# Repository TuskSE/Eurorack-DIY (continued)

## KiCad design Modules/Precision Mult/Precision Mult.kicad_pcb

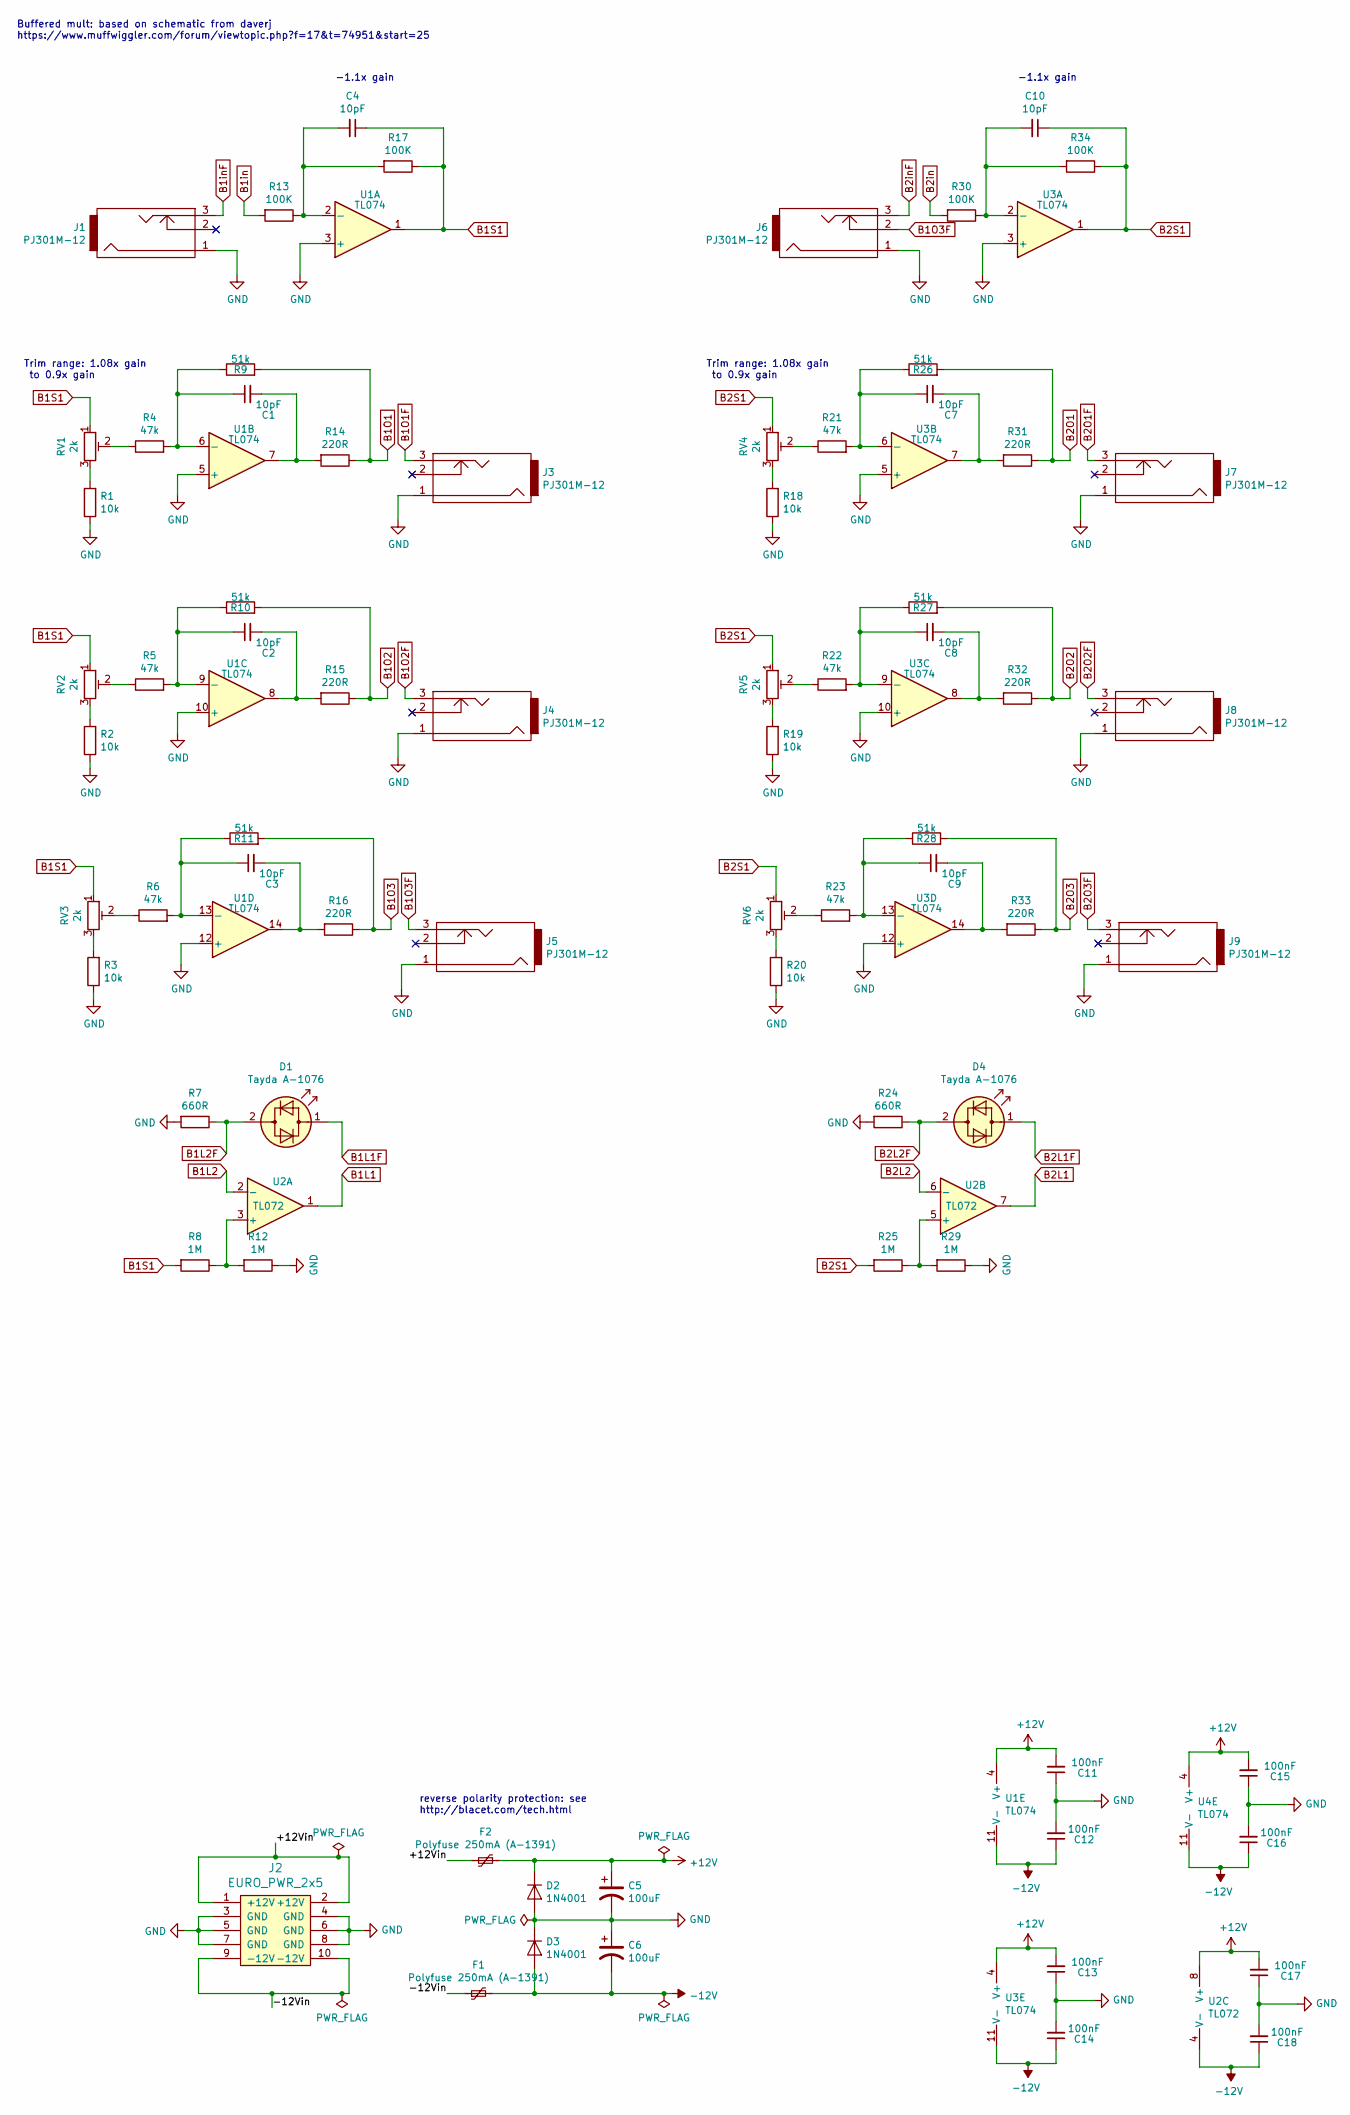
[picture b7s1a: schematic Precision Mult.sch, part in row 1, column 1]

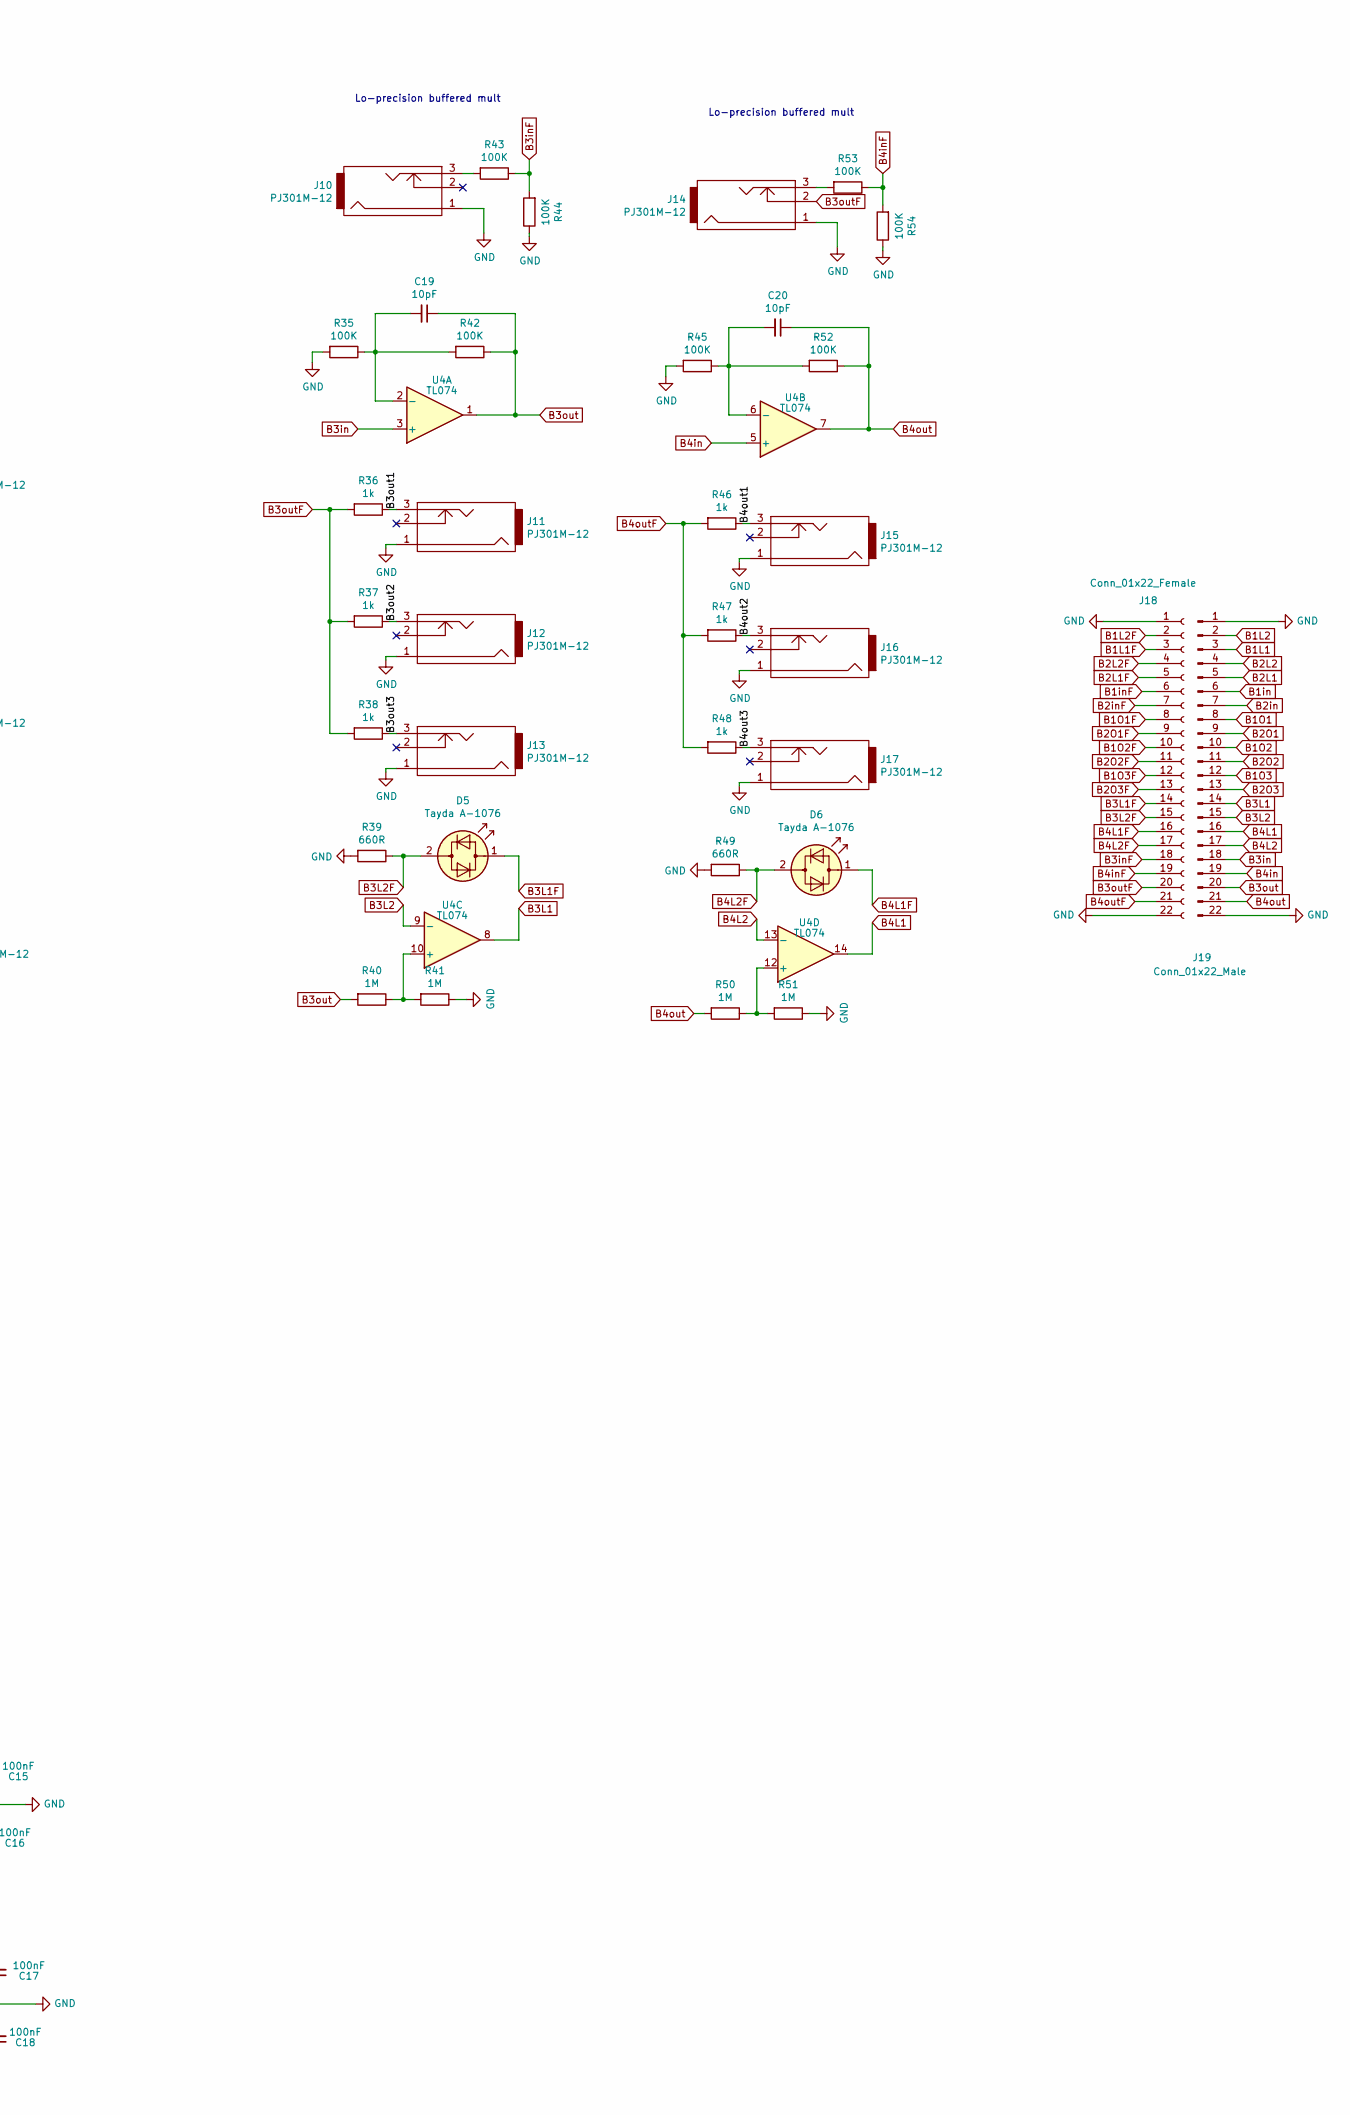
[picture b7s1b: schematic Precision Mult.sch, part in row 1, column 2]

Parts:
C1, C2, C3, C4, C7, C8, C9, C10, C19, C20: 10pF; C_0805_2012Metric_Pad1.15x1.40mm_HandSolder_smallText
C5, C6: 100uF; CP_Radial_D6.3mm_P2.50mm
C11, C12, C13, C14, C15, C16, C17, C18: 100nF; C_0805_2012Metric_Pad1.15x1.40mm_HandSolder_smallText
D1, D4, D5, D6: Tayda A-1076; LED_D3.0mm
D2, D3: 1N4001; D_DO-41_SOD81_P10.16mm_Horizontal
F1, F2: Polyfuse 250mA (A-1391); C_Disc_D7.5mm_W2.5mm_P5.00mm
J1, J3, J4, J5, J6, J7, J8, J9, J10, J11, J12, J13, J14, J15, J16, J17: PJ301M-12; PJ301M-12_Compact
J2: EURO_PWR_2x5; Eurorack_power_header
J18: Conn_01x22_Female; PinSocket_1x22_P2.54mm_Vertical
J19: Conn_01x22_Male; PinSocket_1x22_P2.54mm_Vertical
R1, R2, R3, R18, R19, R20: 10k; R_0805_2012Metric_Pad1.15x1.40mm_HandSolder
R4, R5, R6, R21, R22, R23: 47k; R_0805_2012Metric_Pad1.15x1.40mm_HandSolder
R7, R24, R39, R49: 660R; R_0805_2012Metric_Pad1.15x1.40mm_HandSolder
R8, R12, R25, R29, R40, R41, R50, R51: 1M; R_0805_2012Metric_Pad1.15x1.40mm_HandSolder
R9, R10, R11, R26, R27, R28: 51k; R_0805_2012Metric_Pad1.15x1.40mm_HandSolder
R13, R17, R30, R34, R35, R42, R43, R44, R45, R52, R53, R54: 100K; R_0805_2012Metric_Pad1.15x1.40mm_HandSolder
R14, R15, R16, R31, R32, R33: 220R; R_0805_2012Metric_Pad1.15x1.40mm_HandSolder
R36, R37, R38, R46, R47, R48: 1k; R_0805_2012Metric_Pad1.15x1.40mm_HandSolder
RV1, RV2, RV3, RV4, RV5, RV6: 2k; Potentiometer_Bourns_3296W_Vertical
U1, U3, U4: TL074; SOIC-14_3.9x8.7mm_P1.27mm
U2: TL072; SOIC-8_3.9x4.9mm_P1.27mm

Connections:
+12V: C5.1, C11.2, C13.2, C15.2, C17.2, D2.1 (K), F2.1, U1.4 (V+), U2.8 (V+), U3.4 (V+), U4.4 (V+)
-12V: C6.2, C12.1, C14.1, C16.1, C18.1, D3.2 (A), F1.2, U1.11 (V-), U2.4 (V-), U3.11 (V-), U4.11 (V-)
/+12Vin: F2.2, J2.1 (+12V), J2.2 (+12V)
/-12Vin: F1.1, J2.9 (-12V), J2.10 (-12V)
/B3out1: J11.3, R36.1
/B3out2: J12.3, R37.1
/B3out3: J13.3, R38.1
/B4out1: J15.3, R46.1
/B4out2: J16.3, R47.1
/B4out3: J17.3, R48.1
B1L1: J19.3, U2.1
B1L1F: D1.1 (KA), J18.3
B1L2: J19.2, U2.2 (-)
B1L2F: D1.2 (AK), J18.2, R7.1
B1O1: J19.8, R9.2, R14.1
B1O1F: J3.3, J18.8
B1O2: J19.10, R10.2, R15.1
B1O2F: J4.3, J18.10
B1O3: J19.12, R11.2, R16.1
B1O3F: J5.3, J6.2, J18.12
B1S1: C4.1, R8.2, R17.1, RV1.1, RV2.1, RV3.1, U1.1
B1in: J19.6, R13.2
B1inF: J1.3, J18.6
B2L1: J19.5, U2.7
B2L1F: D4.1 (KA), J18.5
B2L2: J19.4, U2.6 (-)
B2L2F: D4.2 (AK), J18.4, R24.1
B2O1: J19.9, R26.2, R31.1
B2O1F: J7.3, J18.9
B2O2: J19.11, R27.2, R32.1
B2O2F: J8.3, J18.11
B2O3: J19.13, R28.2, R33.1
B2O3F: J9.3, J18.13
B2S1: C10.1, R25.2, R34.1, RV4.1, RV5.1, RV6.1, U3.1
B2in: J19.7, R30.2
B2inF: J6.3, J18.7
B3L1: J19.14, U4.8
B3L1F: D5.1 (KA), J18.14
B3L2: J19.15, U4.9 (-)
B3L2F: D5.2 (AK), J18.15, R39.1
B3in: J19.18, U4.3 (+)
B3inF: J18.18, R43.1, R44.2
B3out: C19.1, J19.20, R40.2, R42.1, U4.1
B3outF: J14.2, J18.20, R36.2, R37.2, R38.2
B4L1: J19.16, U4.14
B4L1F: D6.1 (KA), J18.16
B4L2: J19.17, U4.13 (-)
B4L2F: D6.2 (AK), J18.17, R49.1
B4in: J19.19, U4.5 (+)
B4inF: J18.19, R53.1, R54.2
B4out: C20.1, J19.21, R50.2, R52.1, U4.7
B4outF: J18.21, R46.2, R47.2, R48.2
GND: C5.2, C6.1, C11.1, C12.2, C13.1, C14.2, C15.1, C16.2, C17.1, C18.2, D2.2 (A), D3.1 (K), J1.1, J2.3 (GND), J2.4 (GND), J2.5 (GND), J2.6 (GND), J2.7 (GND), J2.8 (GND), J3.1, J4.1, J5.1, J6.1, J7.1, J8.1, J9.1, J10.1, J11.1, J12.1, J13.1, J14.1, J15.1, J16.1, J17.1, J18.1, J18.22, J19.1, J19.22, R1.1, R2.1, R3.1, R7.2, R12.1, R18.1, R19.1, R20.1, R24.2, R29.1, R35.2, R39.2, R41.1, R44.1, R45.2, R49.2, R51.1, R54.1, U1.3 (+), U1.5 (+), U1.10 (+), U1.12 (+), U3.3 (+), U3.5 (+), U3.10 (+), U3.12 (+)
unnamed: C1.1, R4.2, R9.1, U1.6 (-)
unnamed: C1.2, R14.2, U1.7
unnamed: C2.1, R5.2, R10.1, U1.9 (-)
unnamed: C2.2, R15.2, U1.8
unnamed: C3.1, R6.2, R11.1, U1.13 (-)
unnamed: C3.2, R16.2, U1.14
unnamed: C4.2, R13.1, R17.2, U1.2 (-)
unnamed: C7.1, R21.2, R26.1, U3.6 (-)
unnamed: C7.2, R31.2, U3.7
unnamed: C8.1, R22.2, R27.1, U3.9 (-)
unnamed: C8.2, R32.2, U3.8
unnamed: C9.1, R23.2, R28.1, U3.13 (-)
unnamed: C9.2, R33.2, U3.14
unnamed: C10.2, R30.1, R34.2, U3.2 (-)
unnamed: C19.2, R35.1, R42.2, U4.2 (-)
unnamed: C20.2, R45.1, R52.2, U4.6 (-)
unnamed: J10.3, R43.2
unnamed: J14.3, R53.2
unnamed: R1.2, RV1.3
unnamed: R2.2, RV2.3
unnamed: R3.2, RV3.3
unnamed: R4.1, RV1.2
unnamed: R5.1, RV2.2
unnamed: R6.1, RV3.2
unnamed: R8.1, R12.2, U2.3 (+)
unnamed: R18.2, RV4.3
unnamed: R19.2, RV5.3
unnamed: R20.2, RV6.3
unnamed: R21.1, RV4.2
unnamed: R22.1, RV5.2
unnamed: R23.1, RV6.2
unnamed: R25.1, R29.2, U2.5 (+)
unnamed: R40.1, R41.2, U4.10 (+)
unnamed: R50.1, R51.2, U4.12 (+)

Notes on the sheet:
-1.1x gain
Trim range: 1.08x gain to 0.9x gain
Buffered mult: based on schematic from daverj https://www.muffwiggler.com/forum/viewtopic.php?f=17&t=74951&start=25
reverse polarity protection: see http://blacet.com/tech.html
Lo-precision buffered mult

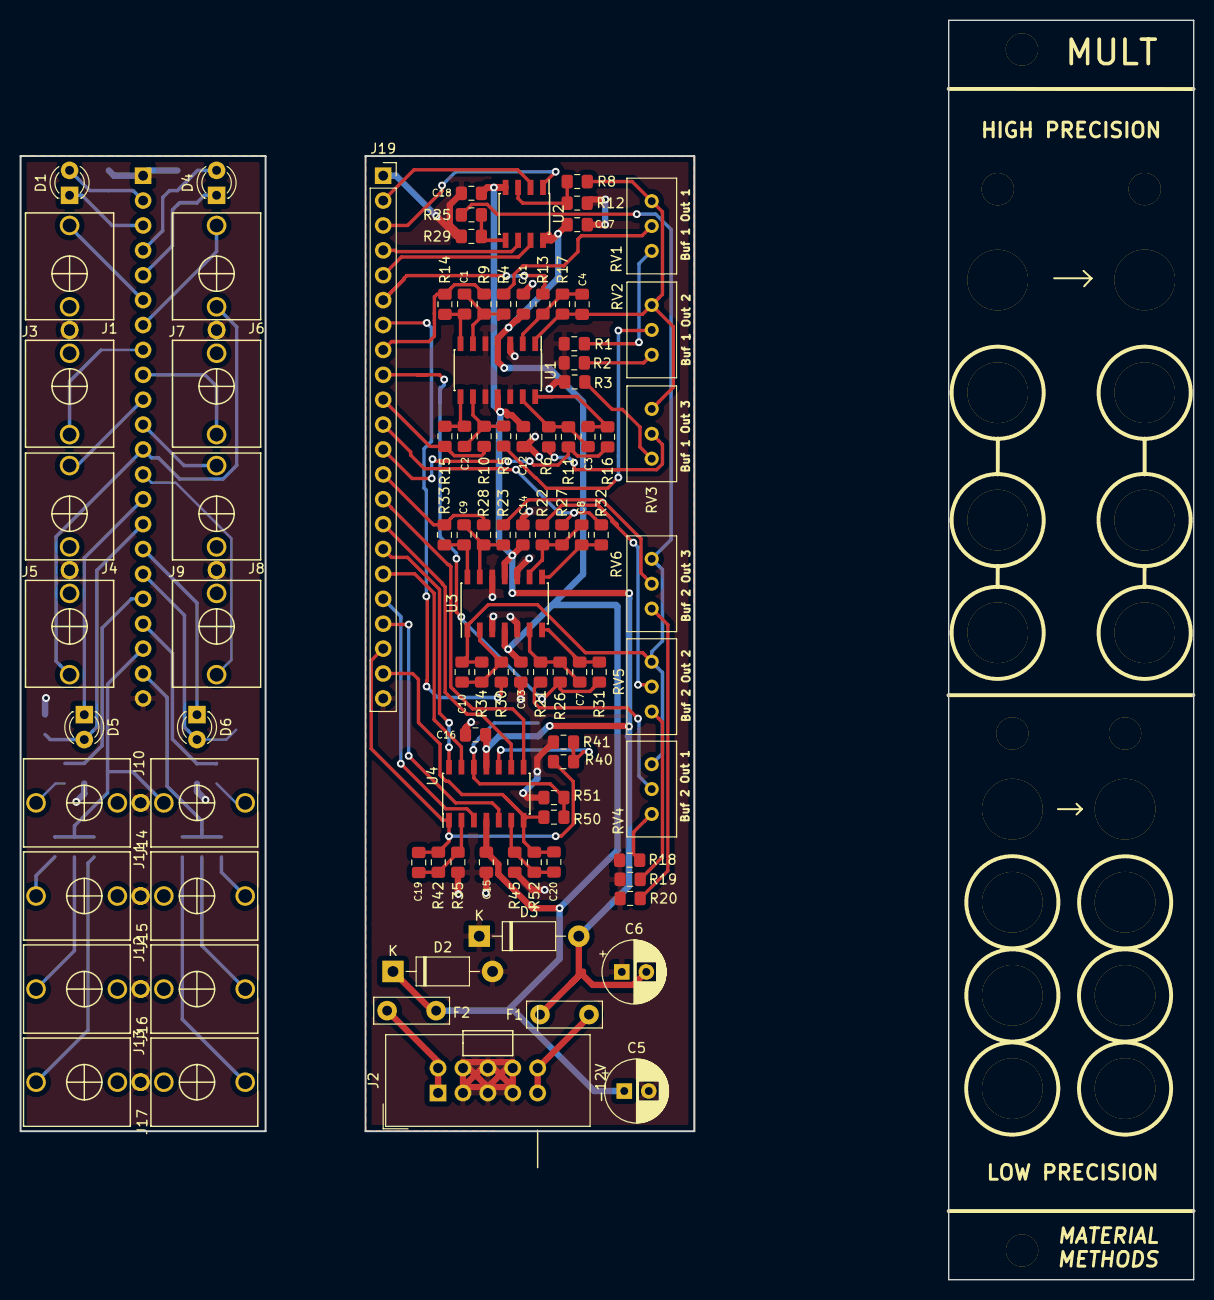
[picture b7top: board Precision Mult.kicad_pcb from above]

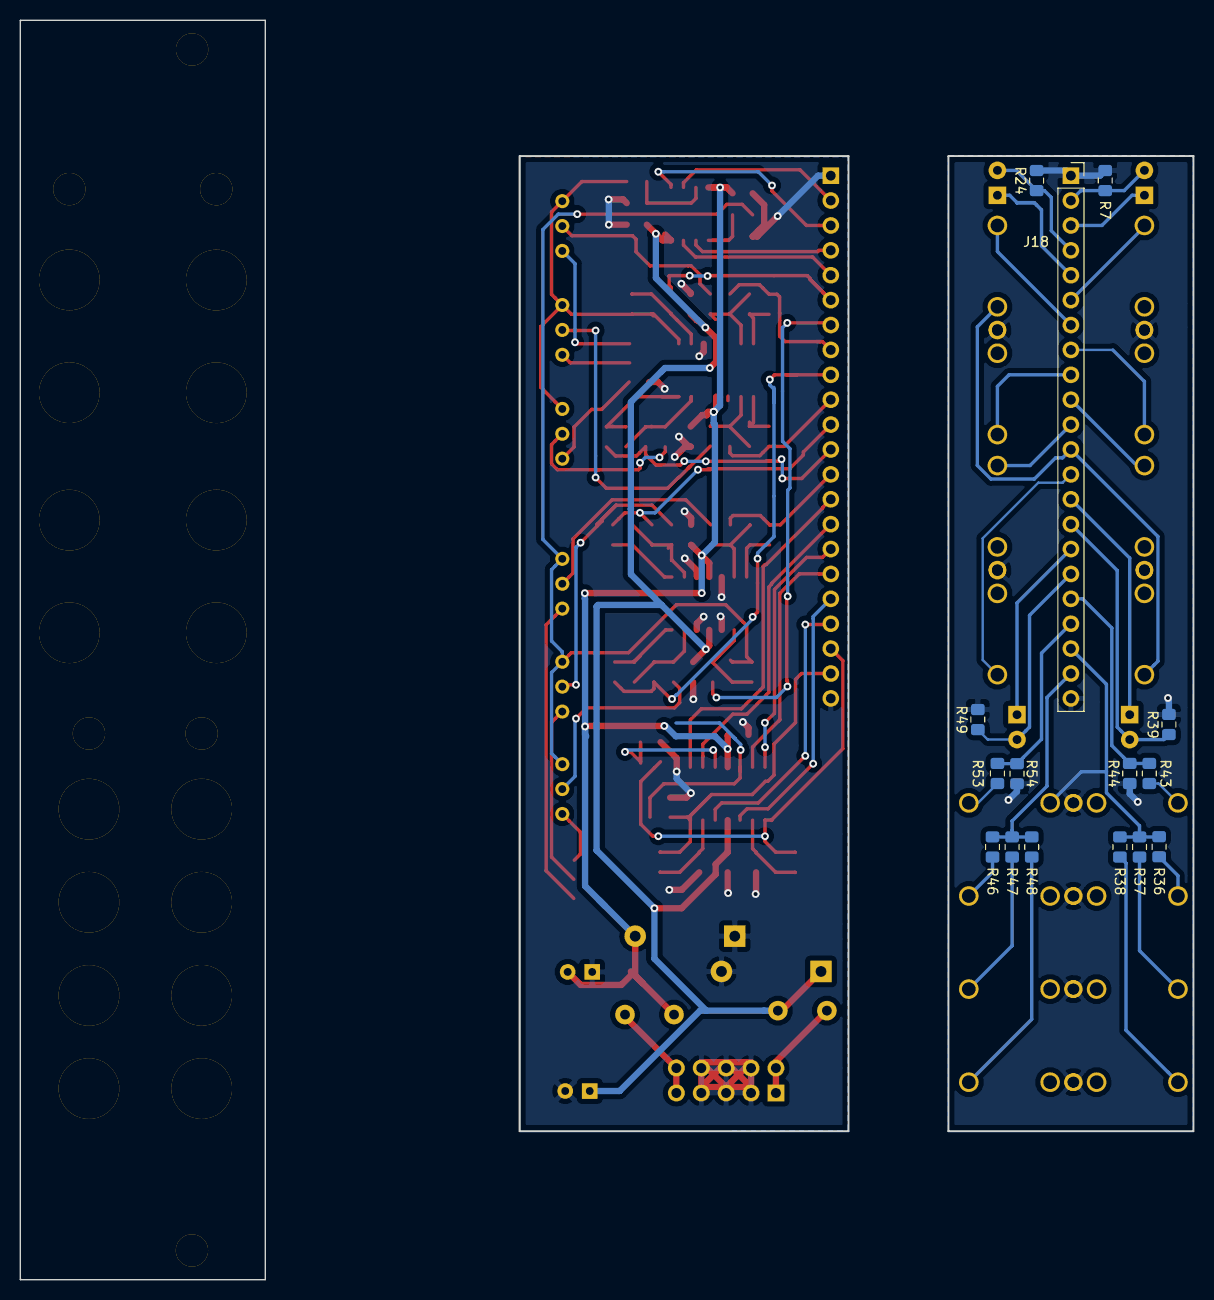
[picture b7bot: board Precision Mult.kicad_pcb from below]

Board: 2 copper layers, 119.7 x 128.5 mm, 111 parts (15 on the bottom side), 87 nets.

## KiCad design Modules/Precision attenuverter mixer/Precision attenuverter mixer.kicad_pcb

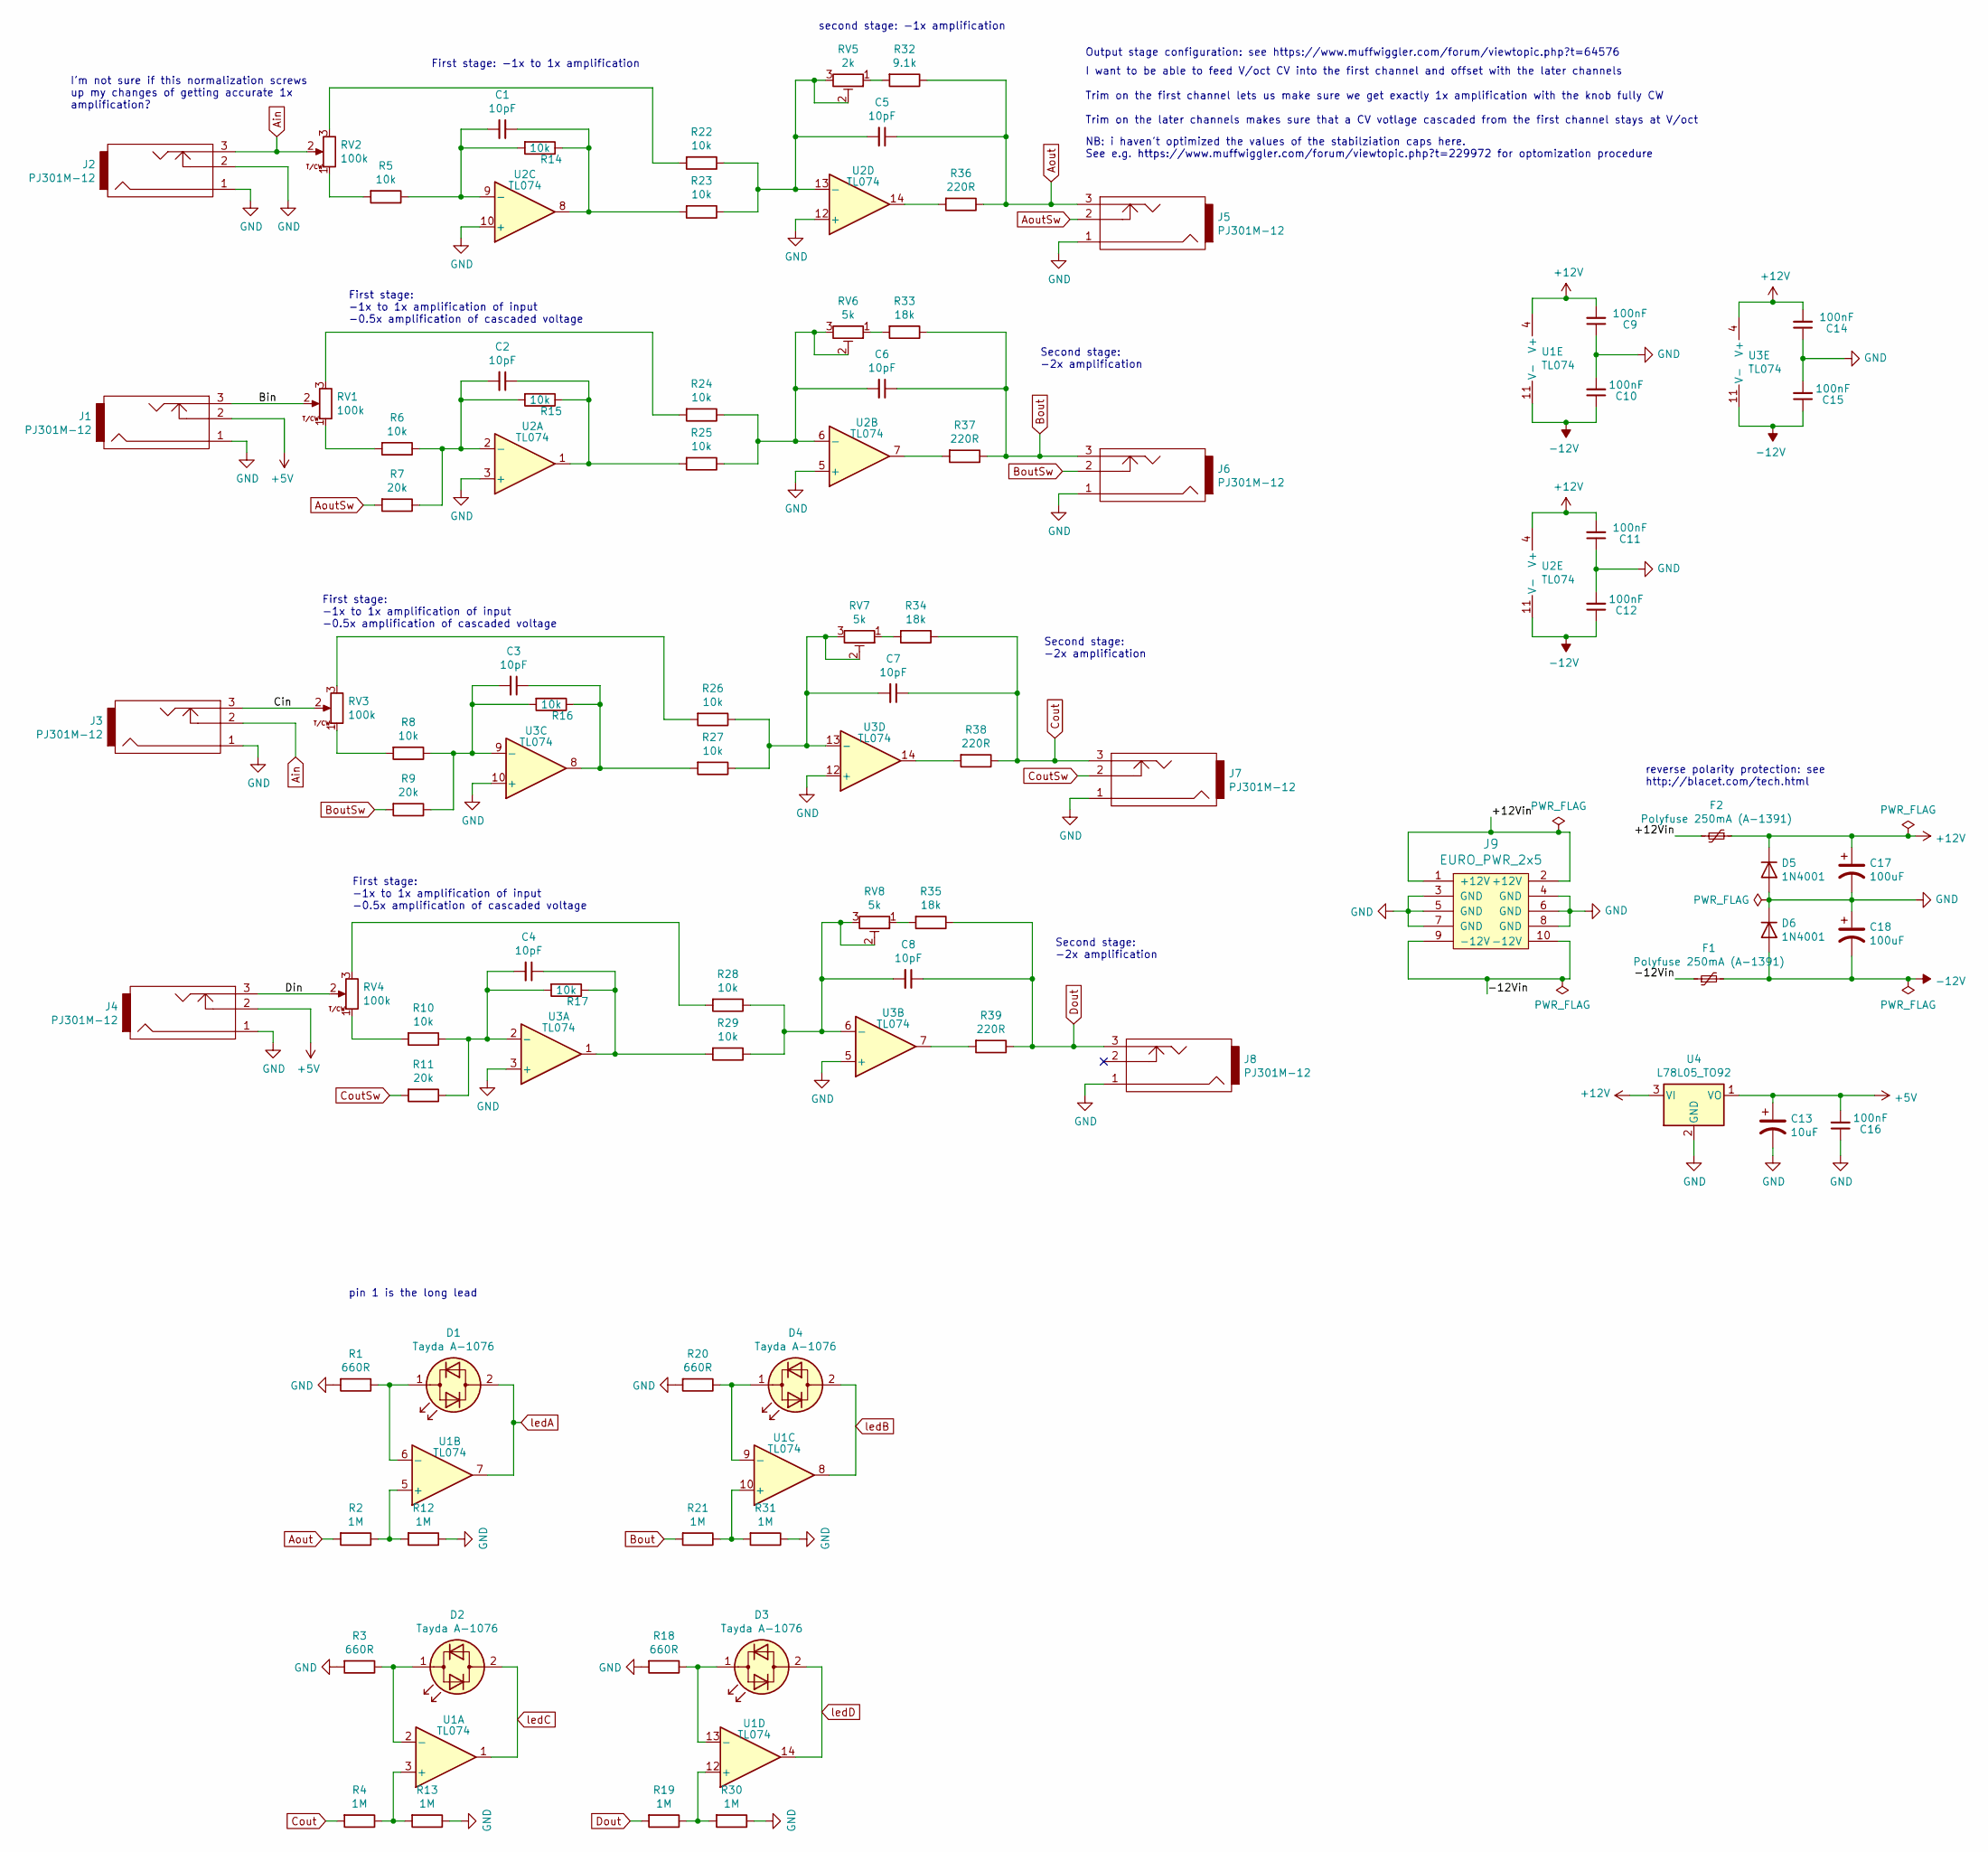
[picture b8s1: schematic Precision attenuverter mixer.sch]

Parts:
C1, C2, C3, C4, C5, C6, C7, C8: 10pF; C_0805_2012Metric_Pad1.15x1.40mm_HandSolder_smallText
C9, C10, C11, C12, C14, C15, C16: 100nF; C_0805_2012Metric_Pad1.15x1.40mm_HandSolder_smallText
C13: 10uF; CP_Radial_D5.0mm_P2.00mm
C17, C18: 100uF; CP_Radial_D6.3mm_P2.50mm
D1, D2, D3, D4: Tayda A-1076; LED_D3.0mm
D5, D6: 1N4001; D_DO-41_SOD81_P10.16mm_Horizontal
F1, F2: Polyfuse 250mA (A-1391); C_Disc_D7.5mm_W2.5mm_P5.00mm
J1, J2, J3, J4, J5, J6, J7, J8: PJ301M-12; PJ301M-12_Compact
J9: EURO_PWR_2x5; Eurorack_power_header
R1, R3, R18, R20: 660R; R_0805_2012Metric_Pad1.15x1.40mm_HandSolder_smallText
R2, R4, R12, R13, R19, R21, R30, R31: 1M; R_0805_2012Metric_Pad1.15x1.40mm_HandSolder_smallText
R5, R6, R8, R10, R14, R15, R16, R17, R22, R23, R24, R25, R26, R27, R28, R29: 10k; R_0805_2012Metric_Pad1.15x1.40mm_HandSolder_smallText
R7, R9, R11: 20k; R_0805_2012Metric_Pad1.15x1.40mm_HandSolder_smallText
R32: 9.1k; R_0805_2012Metric_Pad1.15x1.40mm_HandSolder_smallText
R33, R34, R35: 18k; R_0805_2012Metric_Pad1.15x1.40mm_HandSolder_smallText
R36, R37, R38, R39: 220R; R_0805_2012Metric_Pad1.15x1.40mm_HandSolder_smallText
RV1, RV2, RV3, RV4: 100k; Alpha9mmPot
RV5: 2k; Potentiometer_Bourns_3296W_Vertical
RV6, RV7, RV8: 5k; Potentiometer_Bourns_3296W_Vertical
U1, U2, U3: TL074; SOIC-14_3.9x8.7mm_P1.27mm
U4: L78L05_TO92; TO-92_Inline

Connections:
+5V: C13.1, C16.2, J1.2, J4.2, U4.1 (VO)
+12V: C9.2, C11.2, C14.2, C17.1, D5.1 (K), F2.1, U1.4 (V+), U2.4 (V+), U3.4 (V+), U4.3 (VI)
-12V: C10.1, C12.1, C15.1, C18.2, D6.2 (A), F1.2, U1.11 (V-), U2.11 (V-), U3.11 (V-)
/+12Vin: F2.2, J9.1 (+12V), J9.2 (+12V)
/-12Vin: F1.1, J9.9 (-12V), J9.10 (-12V)
/Bin: J1.3, RV1.2
/Cin: J3.3, RV3.2
/Din: J4.3, RV4.2
Ain: J2.3, J3.2, RV2.2
Aout: C5.1, J5.3, R2.2, R32.1, R36.1
AoutSw: J5.2, R7.2
Bout: C6.1, J6.3, R21.2, R33.1, R37.1
BoutSw: J6.2, R9.2
Cout: C7.1, J7.3, R4.2, R34.1, R38.1
CoutSw: J7.2, R11.2
Dout: C8.1, J8.3, R19.2, R35.1, R39.1
GND: C9.1, C10.2, C11.1, C12.2, C13.2, C14.1, C15.2, C16.1, C17.2, C18.1, D5.2 (A), D6.1 (K), J1.1, J2.1, J2.2, J3.1, J4.1, J5.1, J6.1, J7.1, J8.1, J9.3 (GND), J9.4 (GND), J9.5 (GND), J9.6 (GND), J9.7 (GND), J9.8 (GND), R1.2, R3.2, R12.1, R13.1, R18.2, R20.2, R30.1, R31.1, U2.3 (+), U2.5 (+), U2.10 (+), U2.12 (+), U3.3 (+), U3.5 (+), U3.10 (+), U3.12 (+), U4.2 (GND)
unnamed: C1.1, R14.1, R23.2, U2.8
unnamed: C1.2, R5.1, R14.2, U2.9 (-)
unnamed: C2.1, R15.1, R25.2, U2.1
unnamed: C2.2, R6.1, R7.1, R15.2, U2.2 (-)
unnamed: C3.1, R16.1, R27.2, U3.8
unnamed: C3.2, R8.1, R9.1, R16.2, U3.9 (-)
unnamed: C4.1, R17.1, R29.2, U3.1
unnamed: C4.2, R10.1, R11.1, R17.2, U3.2 (-)
unnamed: C5.2, R22.1, R23.1, RV5.2, RV5.3, U2.13 (-)
unnamed: C6.2, R24.1, R25.1, RV6.2, RV6.3, U2.6 (-)
unnamed: C7.2, R26.1, R27.1, RV7.2, RV7.3, U3.13 (-)
unnamed: C8.2, R28.1, R29.1, RV8.2, RV8.3, U3.6 (-)
unnamed: D1.1 (KA), R1.1, U1.6 (-)
unnamed: D2.1 (KA), R3.1, U1.2 (-)
unnamed: D3.1 (KA), R18.1, U1.13 (-)
unnamed: D4.1 (KA), R20.1, U1.9 (-)
unnamed: R5.2, RV2.1
unnamed: R6.2, RV1.1
unnamed: R8.2, RV3.1
unnamed: R10.2, RV4.1
unnamed: R2.1, R12.2, U1.5 (+)
unnamed: R4.1, R13.2, U1.3 (+)
unnamed: R19.1, R30.2, U1.12 (+)
unnamed: R21.1, R31.2, U1.10 (+)
unnamed: R22.2, RV2.3
unnamed: R24.2, RV1.3
unnamed: R26.2, RV3.3
unnamed: R28.2, RV4.3
unnamed: R32.2, RV5.1
unnamed: R33.2, RV6.1
unnamed: R34.2, RV7.1
unnamed: R35.2, RV8.1
unnamed: R36.2, U2.14
unnamed: R37.2, U2.7
unnamed: R38.2, U3.14
unnamed: R39.2, U3.7
ledA: D1.2 (AK), U1.7
ledB: D4.2 (AK), U1.8
ledC: D2.2 (AK), U1.1
ledD: D3.2 (AK), U1.14

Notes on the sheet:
I'm not sure if this normalization screws up my changes of getting accurate 1x amplification?
Output stage configuration: see https://www.muffwiggler.com/forum/viewtopic.php?t=64576
I want to be able to feed V/oct CV into the first channel and offset with the later channels
Trim on the first channel lets us make sure we get exactly 1x amplification with the knob fully CW Trim on the later channels makes sure that a CV votlage cascaded from the first channel stays at V/oct
NB: i haven't optimized the values of the stabilziation caps here. See e.g. https://www.muffwiggler.com/forum/viewtopic.php?t=229972 for optomization procedure
pin 1 is the long lead
reverse polarity protection: see http://blacet.com/tech.html
First stage: -1x to 1x amplification
second stage: -1x amplification
First stage: -1x to 1x amplification of input -0.5x amplification of cascaded voltage
Second stage: -2x amplification

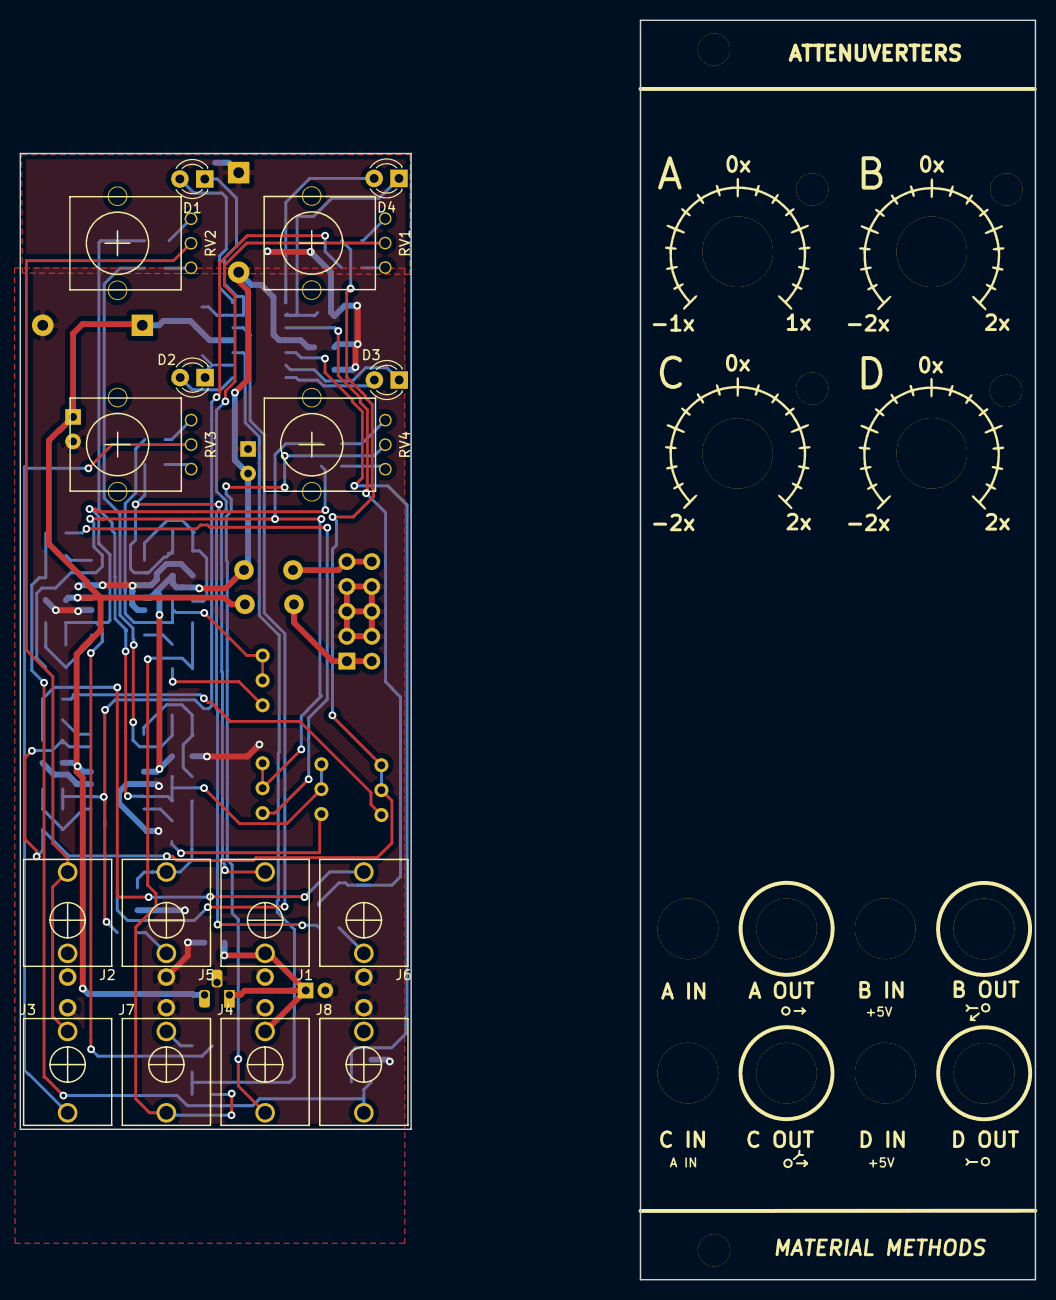
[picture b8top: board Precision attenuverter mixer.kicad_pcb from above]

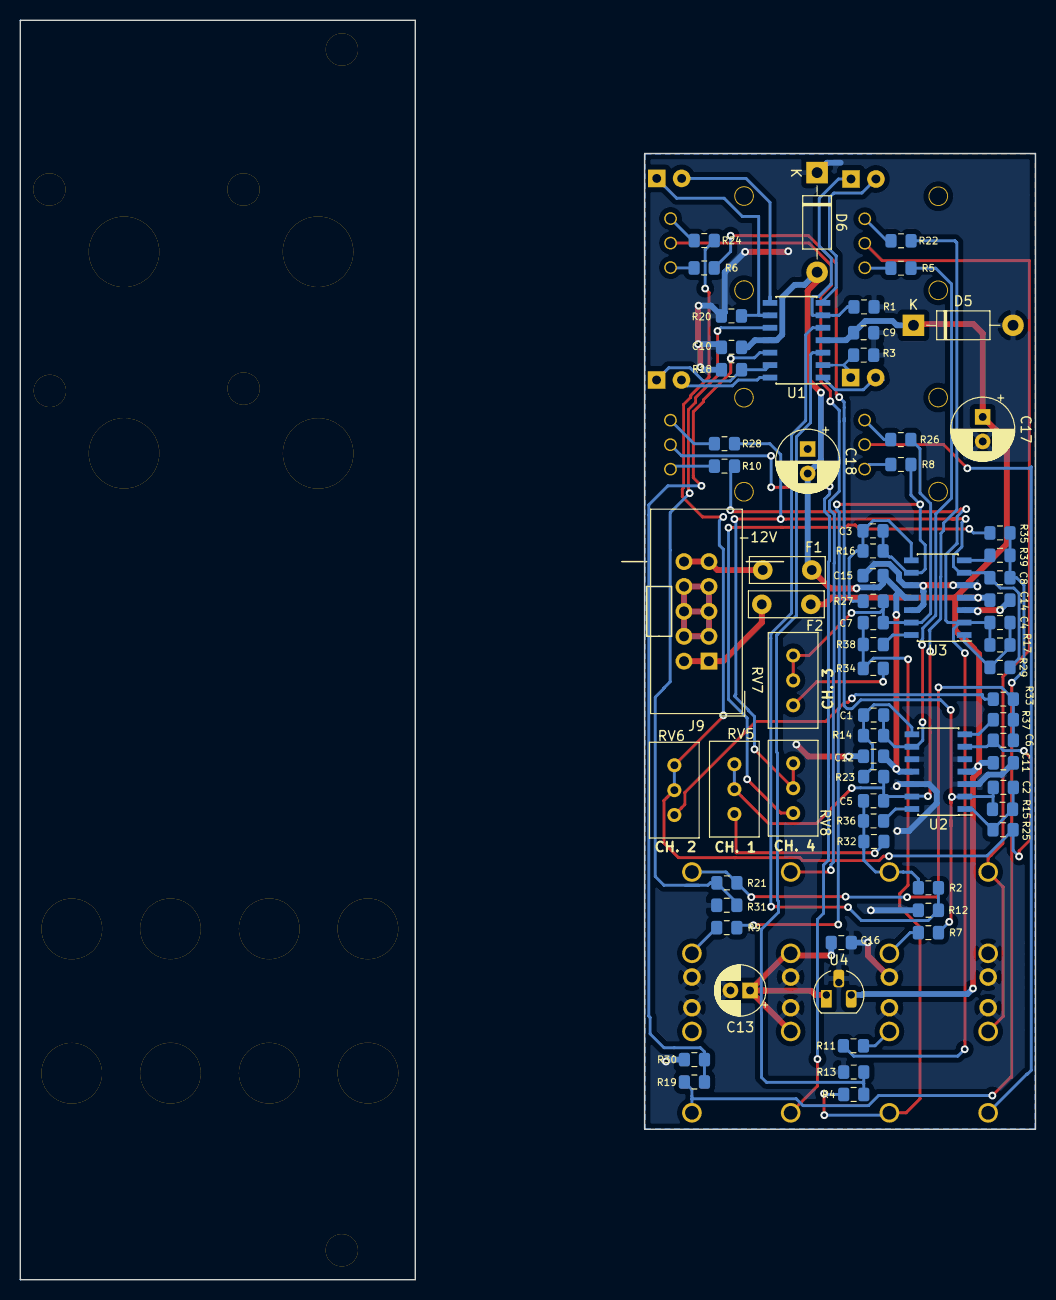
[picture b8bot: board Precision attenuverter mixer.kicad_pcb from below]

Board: 2 copper layers, 39.9 x 99.6 mm, 86 parts (70 on the bottom side), 57 nets.

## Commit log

2021-09-23 Initial commit
    This is a bunch of stuff previously not managed via github - it's a bit of a mess ...
2021-09-23 Initial commit ( tidying up )
2021-09-23 Function generator: tweaked EOC and EOR circuits
    Added diodes to gate outputs to prevent negative "low" value.
    Also tweaked trigger thresholds based on simulations ( EOR comparator )
    Added some additional comments to the schematic
2021-09-26 Board tweaks
    - Changed to zeners with smaller footprint
    - Added board markings
2021-09-26 Minor board tweaks
2021-09-26 Backlink to CADLAB.io has been added.
2021-09-27 Logic neuron tweaks
    - Fixed knob orientations
    - Fixed polarity of stage 4 knob
    - Fixed excessive atenuation at comparator inputs
2021-10-08 Logic neuron schematic update
    Finalized most aspects: just need to assign opamp blocks, and opamp power
2022-01-09 Updated some projects to the new Kicad 6 format
    Updated some projects to the new Kicad 6 format, and ( for the CP3 mixer ) fixed some footprints etc that were broken by the update
2022-01-16 Function generator UI tweaks
    Tweaked Function generator knob placement for more finger space.
2022-01-16 Function generator: added pulldown resistors to gate outputs
2022-01-16 Dual LFO tweaks, Trigger gen brainstorming
    Dual LFO: adjusted normalization markings on the panel, added copper to panel, added JLC board markers
    Brainstormed pot arrangements for random trigger module
2022-01-16 Dual LFO tweaks - very minor
2022-01-17 Logic Neuron Panel Design
    Logic Neuron panel PCB designed, plus a little of the control plate.
    to do next:
    Add channel 4 indicator LED to the schematic
    Divide the schematic into front panel and rear panel components
2022-01-22 Logic Neuron : increased spacing between pots and jacks
    Expanded control board from 100mm high to 110mm to allow more finger space between knobs and jacks.
2022-01-22 Logic Neuron
    Logic Neuron:
    - Added LED indicator for input 4
    - updated some footprints that were broken in the Kicad update
    - started laying out the control board
2022-01-22 Logic Neuron : PCB routing
    Logic Neuron: First pass of PCB routing almost completed.
    To do:
    - ground planes
    - DRCs
    - silkscreen markings
2022-01-23 Logic neuron: PCB layout finished
2022-08-08 Updated readme
    Updated readme with status of the various projects
    Also added photos/renders of the boards for the various projects
    There's also some other additions which are autogenerated by KiCad - don't worry about them...
2022-08-08 cropped some photos
